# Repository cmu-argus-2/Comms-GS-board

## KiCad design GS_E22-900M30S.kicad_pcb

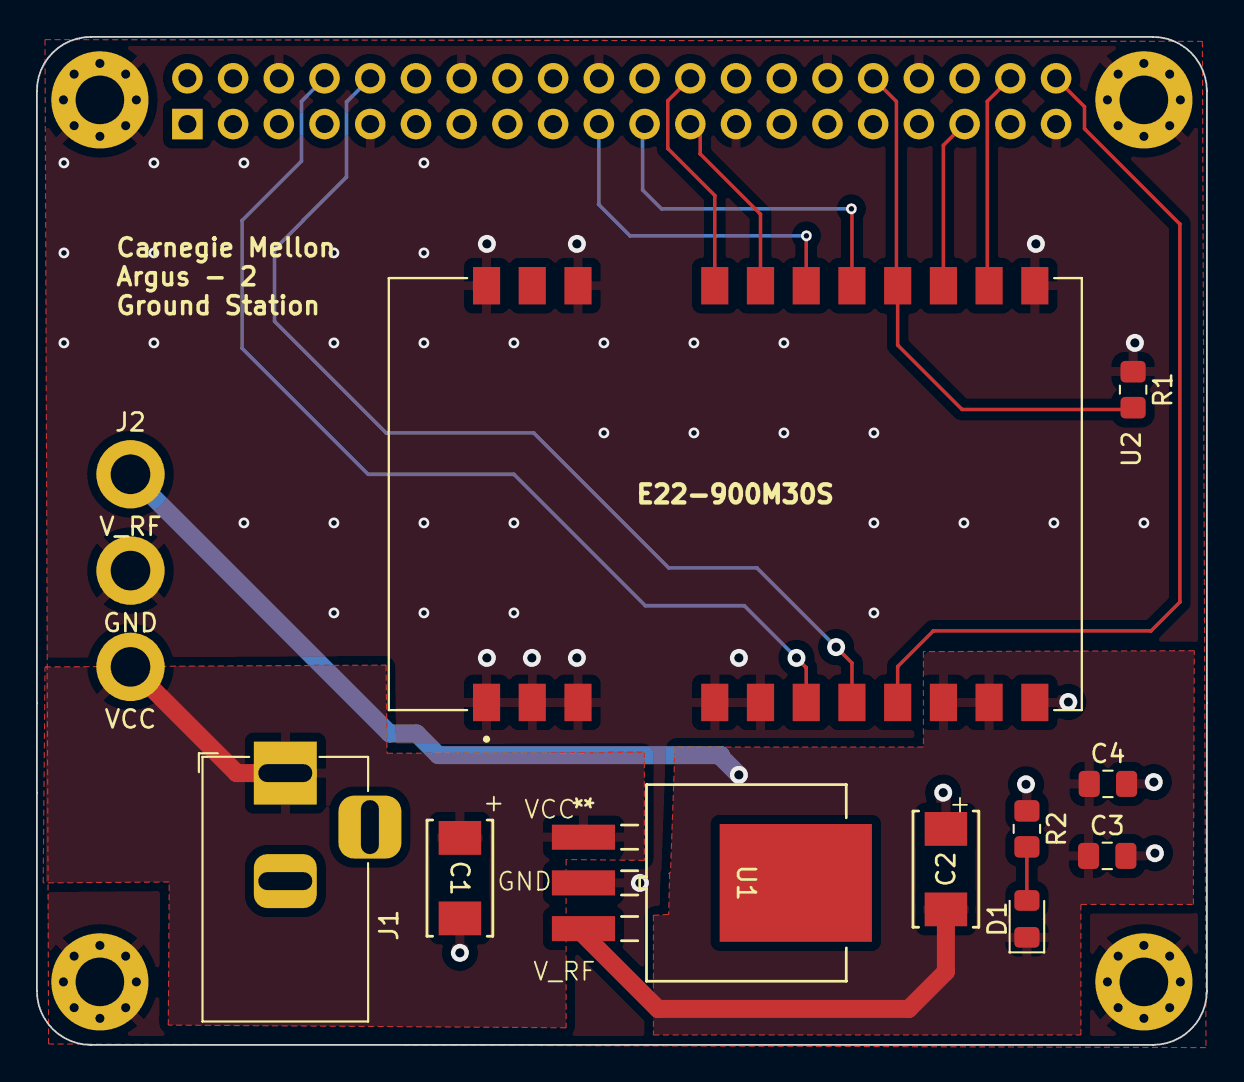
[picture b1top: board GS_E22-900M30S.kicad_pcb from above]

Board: 2 copper layers, 65.0 x 56.0 mm, 18 parts (1 on the bottom side), 14 nets.

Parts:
C1, C2: 10uF; TAJC_AVX
C3: 100nF; C_0805_2012Metric_Pad1.18x1.45mm_HandSolder
C4: 10uF; C_0805_2012Metric_Pad1.18x1.45mm_HandSolder
D1: POW; LED_0805_2012Metric_Pad1.15x1.40mm_HandSolder
H1, H2, H3, H4: M; MountingHole_2.7mm_M2.5_Pad_Via
J1: Barrel_Jack; BarrelJack_Horizontal
J2: V_RF; MountingHole_2.2mm_M2_DIN965_Pad
J3: Raspberry_Pi_2_3; PinSocket_2x20_P2.54mm_Vertical
J4: GND; MountingHole_2.2mm_M2_DIN965_Pad
J5: VCC; MountingHole_2.2mm_M2_DIN965_Pad
R1: 10K; R_0805_2012Metric_Pad1.20x1.40mm_HandSolder
R2: 200; R_0805_2012Metric_Pad1.20x1.40mm_HandSolder
U1: MIC29300-5.0WU-TR; TO-263-3_MCH
U2: E22-900M30S; XCVR_E22-900M30S

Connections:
GND: C1.2, C2.2, C3.2, C4.2, H1.1, H2.1, H3.1, H4.1, J1.2, J3.6 (GND), J3.9 (GND), J3.14 (GND), J3.20 (GND), J3.25 (GND), J3.30 (GND), J3.34 (GND), J3.39 (GND), J4.1, R1.1, R2.1, U1.2 (GND), U2.1 (GND), U2.2 (GND), U2.3 (GND), U2.4 (GND), U2.5 (GND), U2.11 (GND), U2.12 (GND), U2.20 (GND), U2.22 (GND)
unnamed: D1.2 (A), R2.2
RF_BUSY: J3.35 (GPIO19/MISO1), U2.14 (BUSY)
RF_CS: J3.24 (~CE0/GPIO8), U2.19 (NSS)
RF_DIO1: J3.38 (GPIO20/MOSI1), U2.13 (DIO1)
RF_DIO2: J3.40 (GPIO21/SCLK1), U2.8 (DIO2)
RF_MISO: J3.21 (MISO0/GPIO9), U2.16 (MISO)
RF_MOSI: J3.19 (MOSI0/GPIO10), U2.17 (MOSI)
RF_RESET: J3.32 (PWM0/GPIO12), R1.2, U2.15 (~RST)
RF_RXEN: J3.8 (GPIO14/TXD), U2.6 (RXEN)
RF_SCK: J3.23 (SCLK0/GPIO11), U2.18 (SCK)
RF_TXEN: J3.10 (GPIO15/RXD), U2.7 (TXEN)
VCC: C1.1, J1.1, J5.1, U1.1 (IN)
V_RF: C2.1, C3.1, C4.1, D1.1 (K), J2.1, U1.3 (OUT), U2.9 (VCC), U2.10 (VCC)

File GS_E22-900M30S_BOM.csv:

"Id";"Designator";"Footprint";"Quantity";"Designation";"Supplier and ref";
1;"J5";"MountingHole_2.2mm_M2_DIN965_Pad";1;"VCC";;;
2;"H3,H1,H2,H4";"MountingHole_2.7mm_M2.5_Pad_Via";4;"M";;;
3;"J2";"MountingHole_2.2mm_M2_DIN965_Pad";1;"V_RF";;;
4;"U2";"XCVR_E22-900M30S";1;"E22-900M30S";;;
5;"C4";"C_0805_2012Metric_Pad1.18x1.45mm_HandSolder";1;"10uF";;;
6;"R2";"R_0805_2012Metric_Pad1.20x1.40mm_HandSolder";1;"200";;;
7;"C3";"C_0805_2012Metric_Pad1.18x1.45mm_HandSolder";1;"100nF";;;
8;"D1";"LED_0805_2012Metric_Pad1.15x1.40mm_HandSolder";1;"POW";;;
9;"U1";"TO220-3_T_LIT";1;"LT1085-5.0";;;
10;"R1";"R_0805_2012Metric_Pad1.20x1.40mm_HandSolder";1;"10K";;;
11;"J1";"BarrelJack_Horizontal";1;"Barrel_Jack";;;
12;"C1";"TAJC_AVX";1;"10uF";;;
13;"C2";"TAJC_AVX";1;"22uF";;;
14;"J4";"MountingHole_2.2mm_M2_DIN965_Pad";1;"GND";;;
15;"J3";"PinSocket_2x20_P2.54mm_Vertical";1;"Raspberry_Pi_2_3";;;

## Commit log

2024-09-28 Add files via upload
    updated schematic and pcb
2024-09-30 Add files via upload
    updated both schematic and pcb.
2024-09-30 Add files via upload
    updated pcb
2024-09-30 Add files via upload
    libraries for the GS board
2024-10-02 Add files via upload
    updated PCB hopefully final
2024-10-03 Add files via upload
    Final schematic and PCB board
2024-10-03 Add files via upload
    BOM_GS board
2024-10-04 Add files via upload
    Hopefully this is the final version with the SMT voltage regulator with the new schematic as well.
2024-10-05 Add files via upload
    final update
